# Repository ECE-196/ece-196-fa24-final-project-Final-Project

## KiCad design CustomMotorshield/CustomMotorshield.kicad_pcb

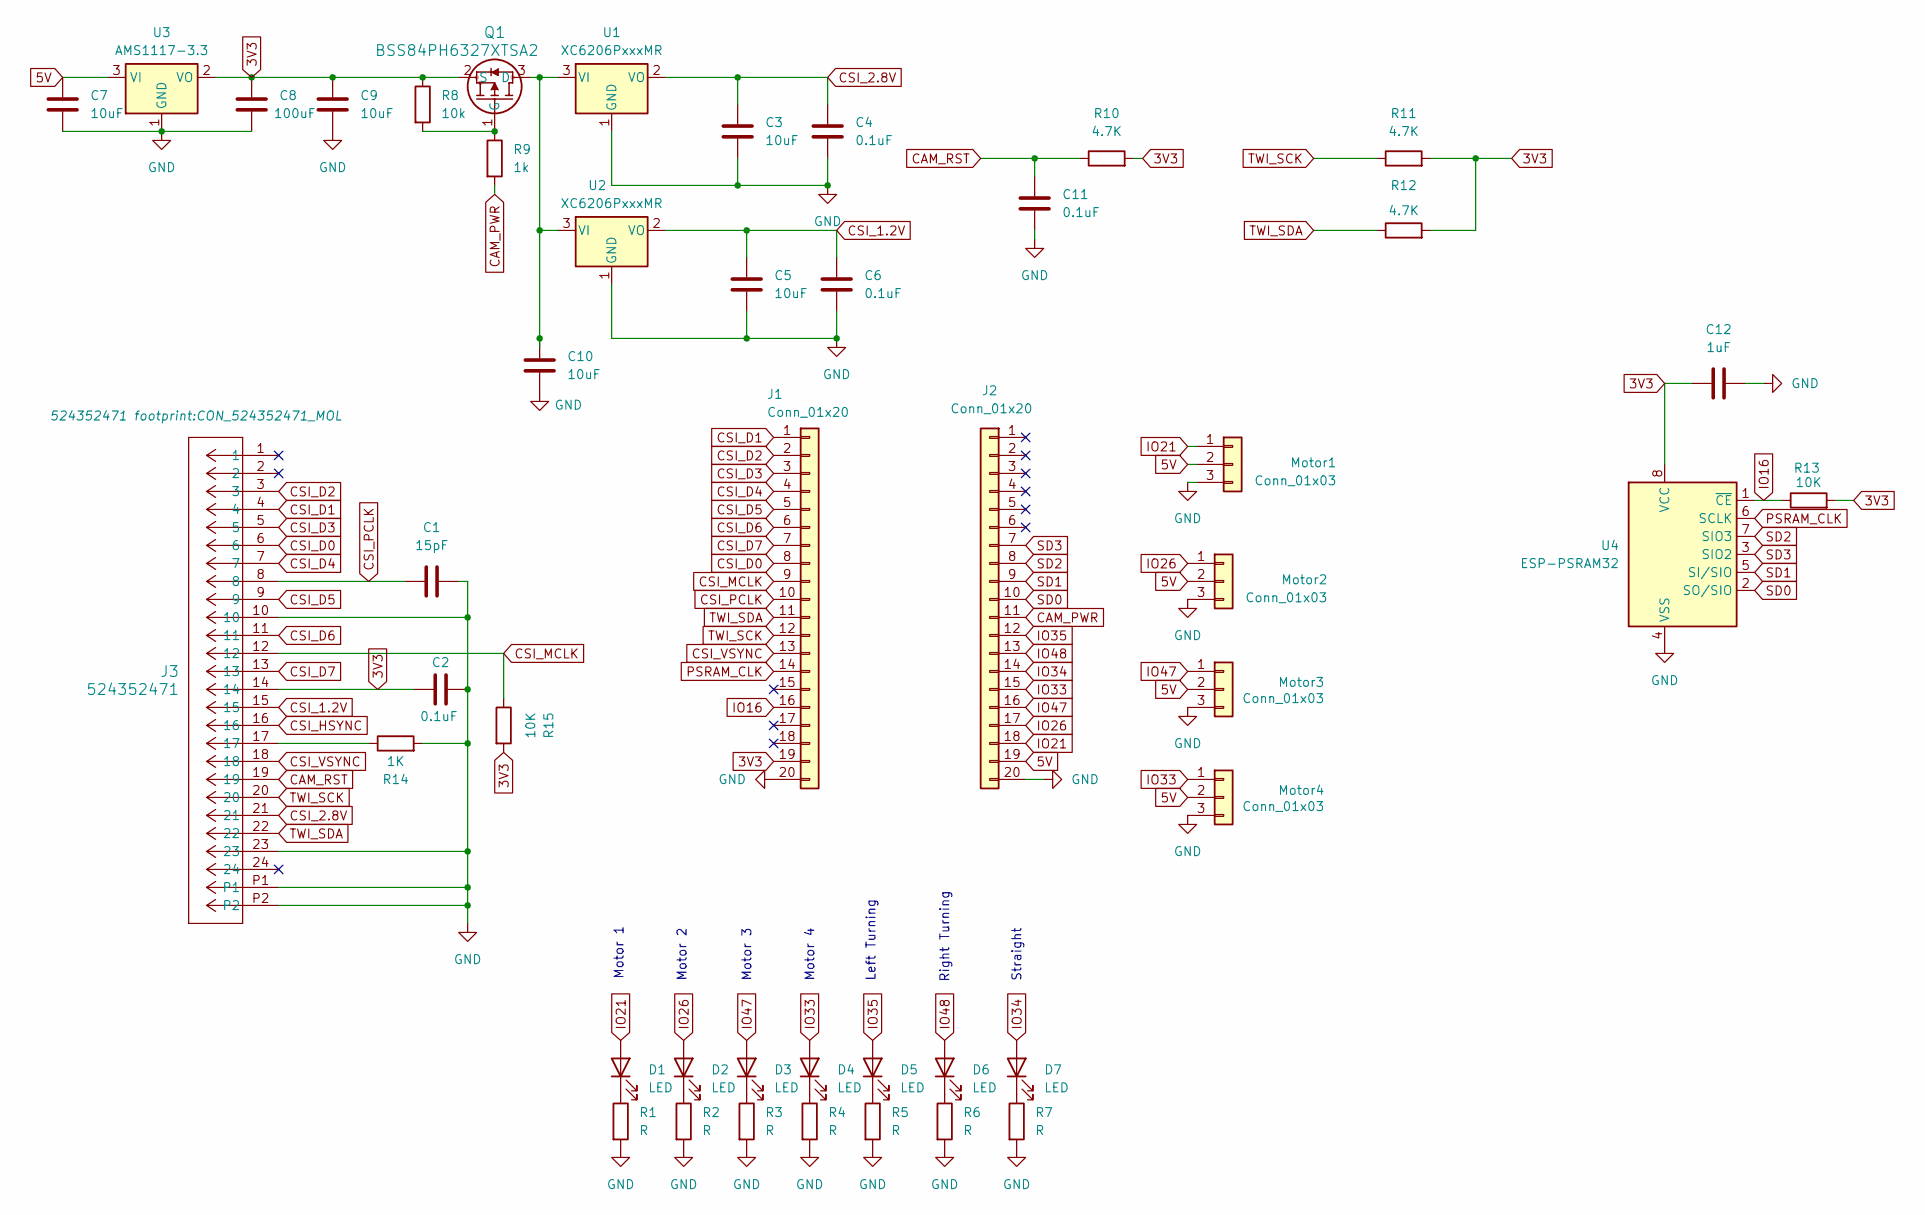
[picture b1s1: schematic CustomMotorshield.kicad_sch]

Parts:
C1: 15pF; C_0603_1608Metric_Pad1.08x0.95mm_HandSolder
C2, C4, C6, C11: 0.1uF; C_0603_1608Metric_Pad1.08x0.95mm_HandSolder
C3, C5, C7, C9, C10: 10uF; C_0603_1608Metric_Pad1.08x0.95mm_HandSolder
C8: 100uF; C_0603_1608Metric_Pad1.08x0.95mm_HandSolder
C12: 1uF; C_0603_1608Metric_Pad1.08x0.95mm_HandSolder
D1, D2, D3, D4, D5, D6, D7: LED; LED_0603_1608Metric_Pad1.05x0.95mm_HandSolder
J1, J2: Conn_01x20; PinHeader_1x20_P2.54mm_Vertical
J3: 524352471; CON_524352471_MOL
Motor1, Motor2, Motor3, Motor4: Conn_01x03; JST_EH_B3B-EH-A_1x03_P2.50mm_Vertical
Q1: BSS84PH6327XTSA2; SOT23_BSS84_INF
R1, R2, R3, R4, R5, R6, R7: R; R_0603_1608Metric_Pad0.98x0.95mm_HandSolder
R8: 10k; R_0603_1608Metric_Pad0.98x0.95mm_HandSolder
R9: 1k; R_0603_1608Metric_Pad0.98x0.95mm_HandSolder
R10, R11, R12: 4.7K; R_0603_1608Metric_Pad0.98x0.95mm_HandSolder
R13, R15: 10K; R_0603_1608Metric_Pad0.98x0.95mm_HandSolder
R14: 1K; R_0603_1608Metric_Pad0.98x0.95mm_HandSolder
U1, U2: XC6206PxxxMR; SOT-23-3
U3: AMS1117-3.3; SOT-223-3_TabPin2
U4: ESP-PSRAM32; SOIC-8_3.9x4.9mm_P1.27mm

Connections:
3V3: C2.1, C8.1, C9.1, C12.1, J1.19, J3.14, Q1.2 (S), R8.1, R10.2, R11.2, R12.2, R13.2, R15.2, U3.2 (VO), U4.8 (VCC); also elsewhere on the board
5V: C7.1, J2.19, Motor1.2, Motor2.2, Motor3.2, Motor4.2, U3.3 (VI); also elsewhere on the board
CAM_PWR: J2.11, R9.2
CAM_RST: C11.1, J3.19, R10.1
CSI_1.2V: C5.1, C6.1, J3.15, U2.2 (VO)
CSI_2.8V: C3.1, C4.1, J3.21, U1.2 (VO)
CSI_D0: J1.8, J3.6
CSI_D1: J1.1, J3.4
CSI_D2: J1.2, J3.3
CSI_D3: J1.3, J3.5
CSI_D4: J1.4, J3.7
CSI_D5: J1.5, J3.9
CSI_D6: J1.6, J3.11
CSI_D7: J1.7, J3.13
CSI_HSYNC: J3.16
CSI_MCLK: J1.9, J3.12, R15.1
CSI_PCLK: C1.1, J1.10, J3.8
CSI_VSYNC: J1.13, J3.18
GND: C1.2, C2.2, C3.2, C4.2, C5.2, C6.2, C7.2, C8.2, C9.2, C10.2, C11.2, C12.2, J1.20, J2.20, J3.10, J3.23, J3.P1, J3.P2, Motor1.3, Motor2.3, Motor3.3, Motor4.3, R1.2, R2.2, R3.2, R4.2, R5.2, R6.2, R7.2, R14.2, U1.1 (GND), U2.1 (GND), U3.1 (GND), U4.4 (VSS); also elsewhere on the board
IO16: J1.16, R13.1, U4.1 (~CE)
IO21: D1.2 (A), J2.18, Motor1.1
IO26: D2.2 (A), J2.17, Motor2.1
IO33: D4.2 (A), J2.15, Motor4.1
IO34: D7.2 (A), J2.14
IO35: D5.2 (A), J2.12
IO47: D3.2 (A), J2.16, Motor3.1
IO48: D6.2 (A), J2.13
unnamed: D1.1 (K), R1.1
unnamed: D2.1 (K), R2.1
unnamed: D3.1 (K), R3.1
unnamed: D4.1 (K), R4.1
unnamed: D5.1 (K), R5.1
unnamed: D6.1 (K), R6.1
unnamed: D7.1 (K), R7.1
unnamed: J3.17, R14.1
unnamed: C10.1, Q1.3 (D), U1.3 (VI), U2.3 (VI)
unnamed: Q1.1 (G), R8.2, R9.1
PSRAM_CLK: J1.14, U4.6 (SCLK)
SD0: J2.10, U4.2 (SO/SIO)
SD1: J2.9, U4.5 (SI/SIO)
SD2: J2.8, U4.7 (SIO3)
SD3: J2.7, U4.3 (SIO2)
TWI_SCK: J1.12, J3.20, R11.1
TWI_SDA: J1.11, J3.22, R12.1

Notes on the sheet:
Motor 4
Motor 1
Straight
Right Turning
Motor 3
Motor 2
Left Turning

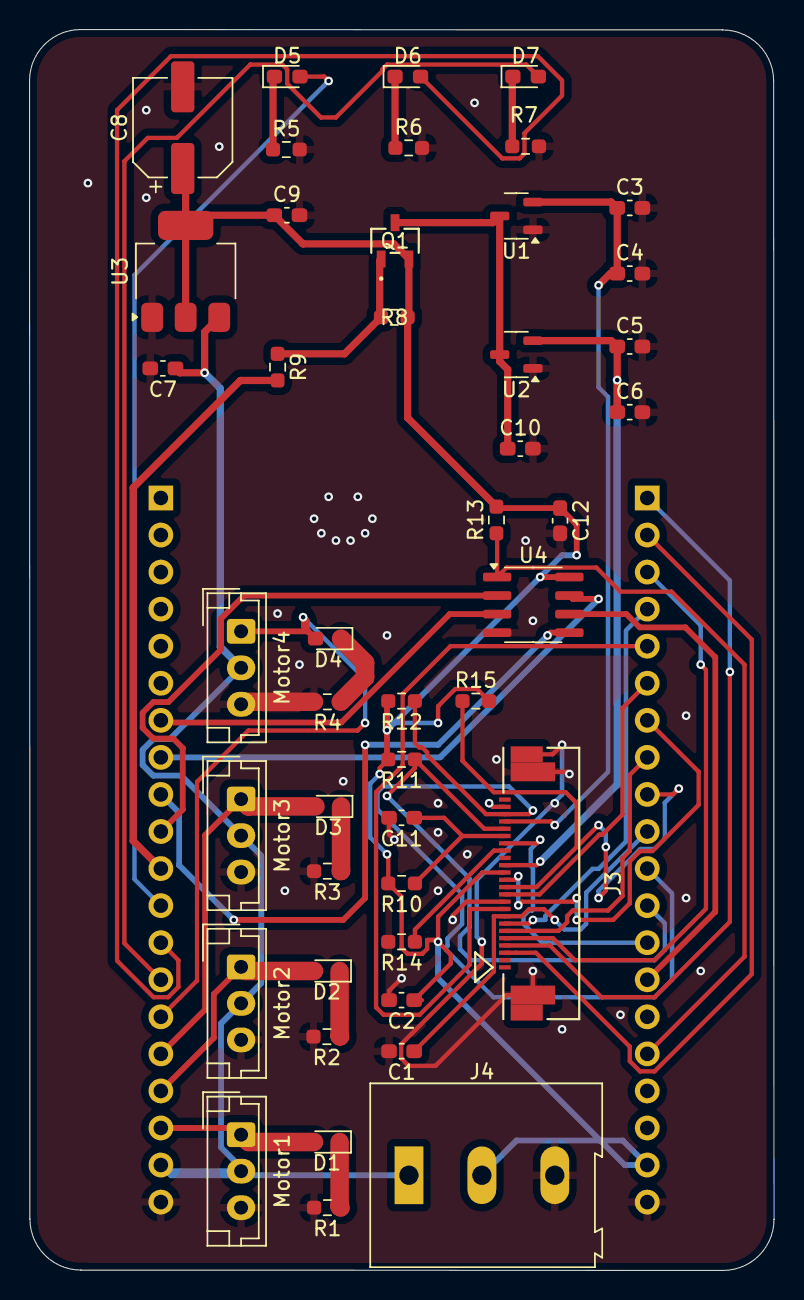
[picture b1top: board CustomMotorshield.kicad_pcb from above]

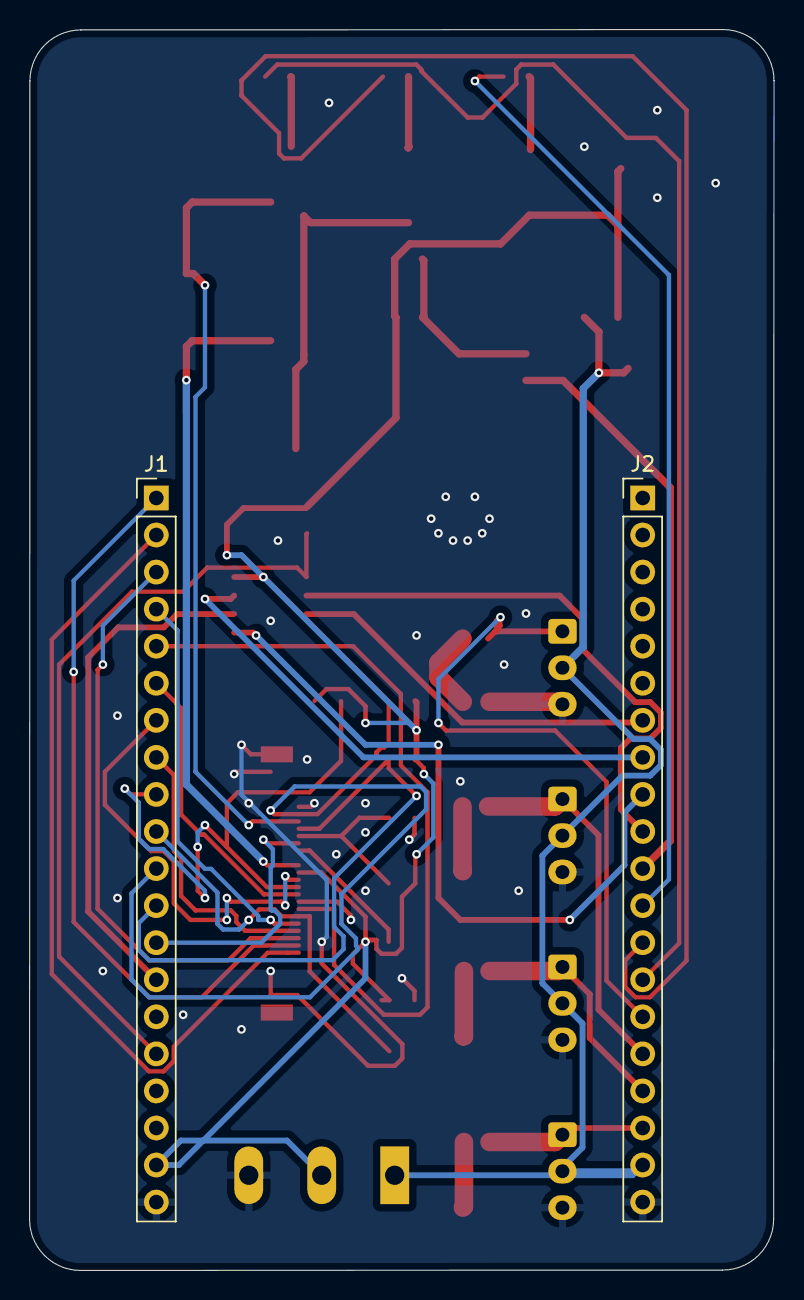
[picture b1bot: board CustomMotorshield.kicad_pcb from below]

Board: 2 copper layers, 51.0 x 85.1 mm, 47 parts (2 on the bottom side), 43 nets.

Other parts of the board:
J4: Screw_Terminal_01x03; TerminalBlock_Altech_AK300-3_P5.00mm

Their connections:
3V3: J4.2; also elsewhere on the board
5V: J4.1; also elsewhere on the board
GND: J4.3; also elsewhere on the board

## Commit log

2024-10-18 Updated Proposal
    Added parts list link and actual table in the document.
2024-10-28 PCB Submission !
2024-10-30 Updated PCB !
2024-10-31 Latest PCB !
2024-10-31 new PCB with VR
2024-10-31 pcb :)
2024-10-31 gerber and drill
2024-11-04 Create website
